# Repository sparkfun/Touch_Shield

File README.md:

**NOTE:** *This product has been retired from our catalog. If you are looking for more up-to-date info, please check out some of these resources to see how other users are still hacking and improving on this product.*
* *[SparkFun Forum](https://forum.sparkfun.com/)*
* *[Comments Here on GitHub](https://github.com/sparkfun/Touch_Shield/issues)*
* *[IRC Channel](https://www.sparkfun.com/news/263)*

Touch Shield
============

[  
*Touch Shield (DEV-12013)*](https://www.sparkfun.com/products/12013)

The Touch Shield allows you to easily interface the MPR121 IC to your Arduino. It has 9 capacitive touch pads,
with headers for the remaining 3 electrode connections. 

Repository Contents
-------------------
* **/Firmware** - Example firmware for interfacing with the Touch Shield
* **/Hardware** - All Eagle board design files (.brd, .sch)
* **/Production** - Test bed files and production panel files

Product Versions
----------------
* [DEV-10508](https://www.sparkfun.com/products/10508)- Basic Touch Shield
* [RTL-10774](https://www.sparkfun.com/products/10774)- Retail packaging of the Touch Shield and Arduino stackable headers

Version History
---------------
* [DEV-10508](https://www.sparkfun.com/products/10508) Version 1.1

License Information
-------------------
The hardware is released under [Creative Commons Share-alike 3.0](http://creativecommons.org/licenses/by-sa/3.0/).  
All other code is open source so please feel free to do anything you want with it; you buy me a beer if you use this and we meet someday ([Beerware license](http://en.wikipedia.org/wiki/Beerware)).

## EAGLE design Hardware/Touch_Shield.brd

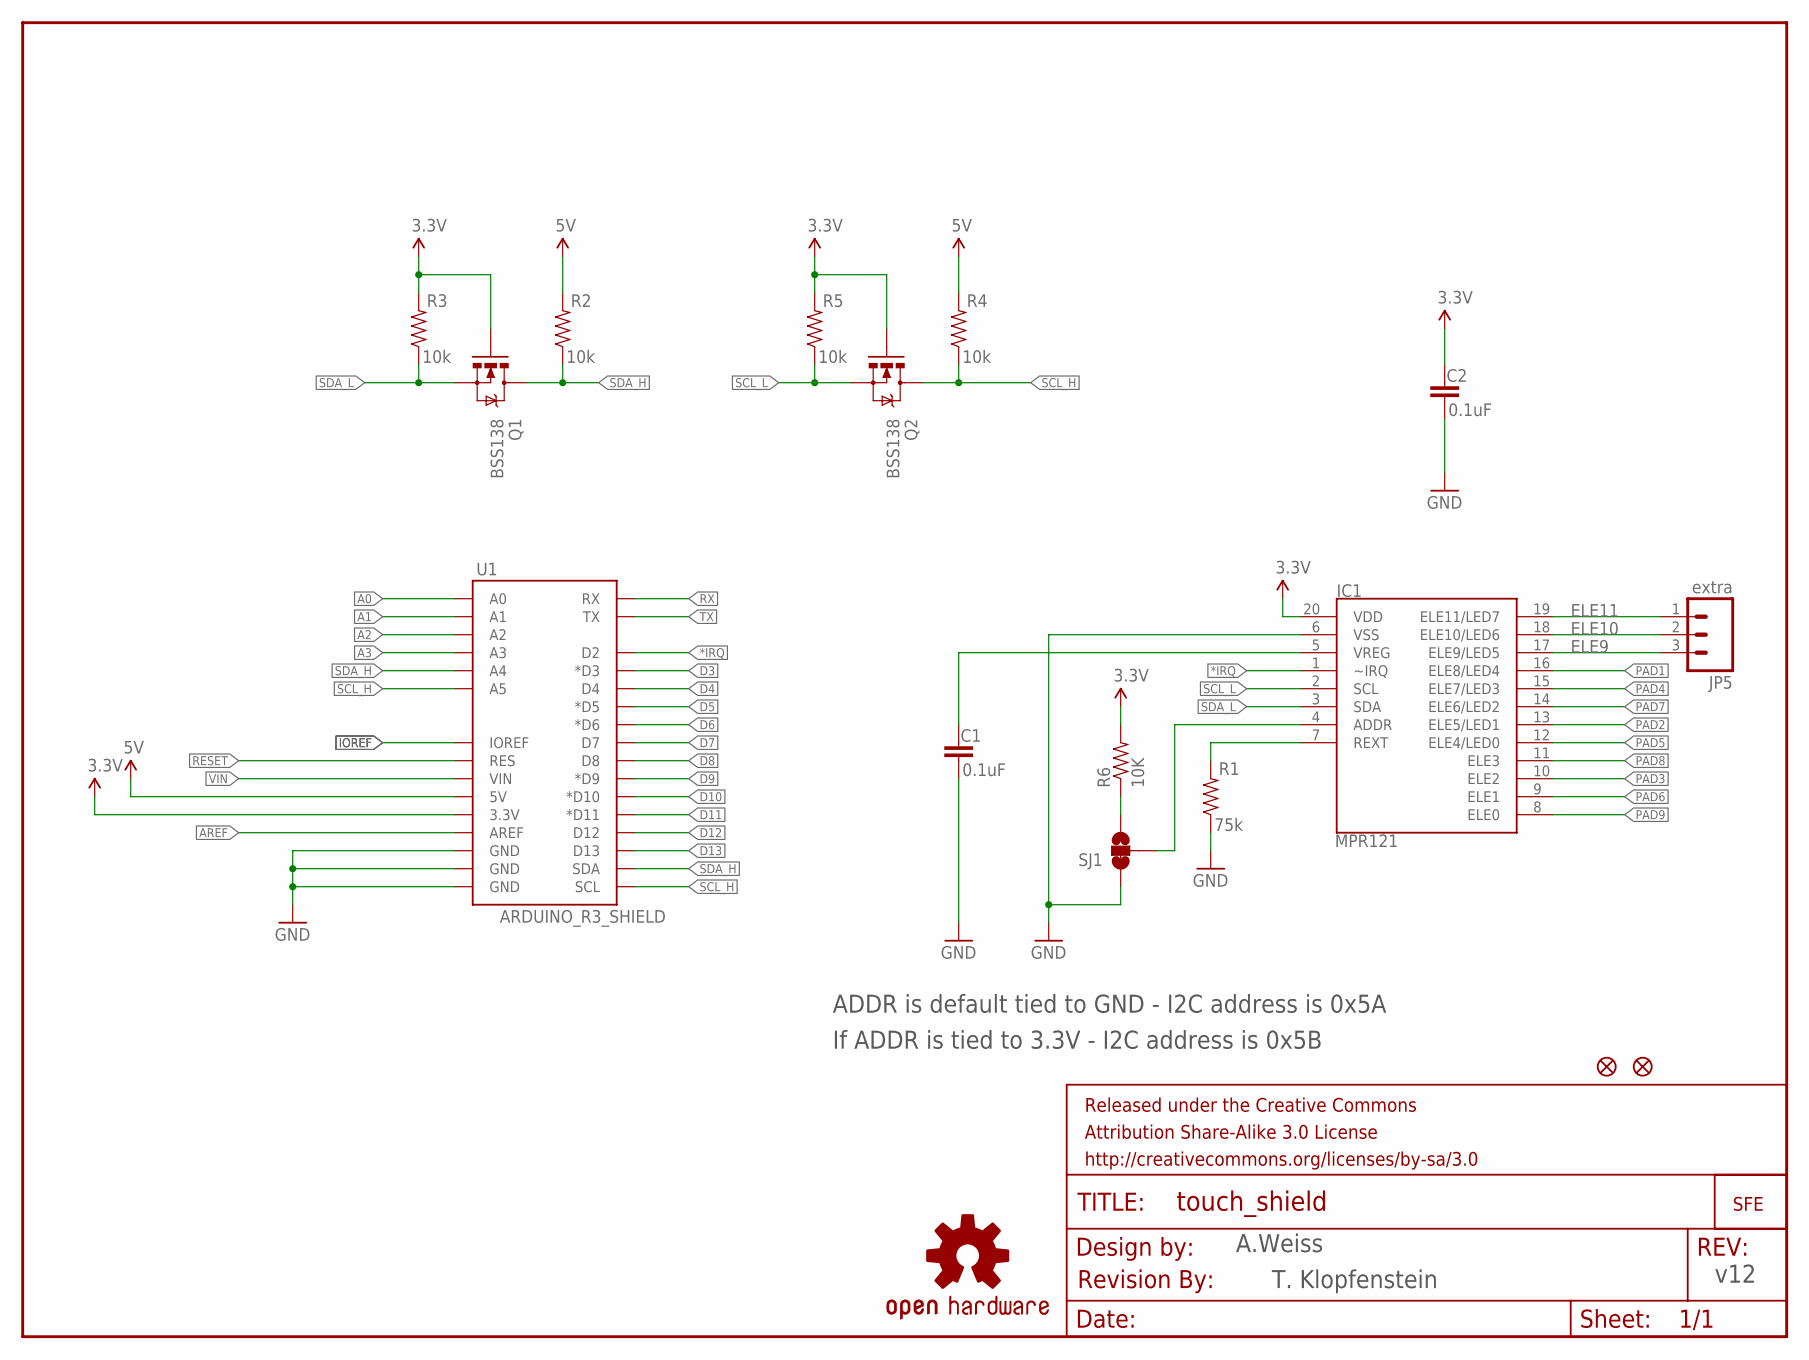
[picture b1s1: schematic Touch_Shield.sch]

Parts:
C1, C2: 0.1uF; 0603-CAP
FID1, FID2: FIDUCIALUFIDUCIAL; MICRO-FIDUCIAL
FRAME1: FRAME-LETTER; CREATIVE_COMMONS
IC1: MPR121; QFN-20-0.4MM-V2
JP1: LOGO-SFENEW; SFE-NEW-WEBLOGO
JP5: extra; 1X03
Q1, Q2: BSS138; SOT23-3
R1: 75k; 0603-RES
R2, R3, R4, R5: 10k; 0603-RES
R6: 10K; 0603-RES
SJ1: SOLDERJUMPER_2WAYPASTE1&2; SJ_3_PASTE1&2
U1: ARDUINO_R3_SHIELD; UNO_R3_SHIELD
U$1: REVISION
U$5: OSHW-LOGOL; OSHW-LOGO-L

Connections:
3.3V: C2.1, IC1.20 (VDD), Q1.1 (G), Q2.1 (G), R3.2, R5.2, R6.2, U1.3.3V
5V: R2.2, R4.2, U1.5V
*IRQ: IC1.1 (~IRQ), U1.D2
A0: U1.A0
A1: U1.A1
A2: U1.A2
A3: U1.A3
AREF: U1.AREF
D3: U1.D3 (*D3)
D4: U1.D4
D5: U1.D5 (*D5)
D6: U1.D6 (*D6)
D7: U1.D7
D8: U1.D8
D9: U1.D9 (*D9)
D10: U1.D10 (*D10)
D11: U1.D11 (*D11)
D12: U1.D12
D13: U1.D13
ELE9: IC1.17 (ELE9/LED5), JP5.3
ELE10: IC1.18 (ELE10/LED6), JP5.2
ELE11: IC1.19 (ELE11/LED7), JP5.1
GND: C1.2, C2.2, IC1.6 (VSS), R1.1, SJ1.1, U1.GND@0 (GND), U1.GND@1 (GND), U1.GND@2 (GND)
IOREF: U1.IOREF
unnamed: IC1.4 (ADDR), SJ1.2
unnamed: R6.1, SJ1.3
PAD1: IC1.16 (ELE8/LED4)
PAD2: IC1.13 (ELE5/LED1)
PAD3: IC1.10 (ELE2)
PAD4: IC1.15 (ELE7/LED3)
PAD5: IC1.12 (ELE4/LED0)
PAD6: IC1.9 (ELE1)
PAD7: IC1.14 (ELE6/LED2)
PAD8: IC1.11 (ELE3)
PAD9: IC1.8 (ELE0)
RESET: U1.RES
REXT: IC1.7 (REXT), R1.2
RX: U1.RX
SCL_H: Q2.3 (D), R4.1, U1.A5, U1.SCL
SCL_L: IC1.2 (SCL), Q2.2 (S), R5.1
SDA_H: Q1.3 (D), R2.1, U1.A4, U1.SDA
SDA_L: IC1.3 (SDA), Q1.2 (S), R3.1
TX: U1.TX
VIN: U1.VIN
VREG: C1.1, IC1.5 (VREG)

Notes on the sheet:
A.Weiss
ADDR is default tied to GND - I2C address is 0x5A
v12
T. Klopfenstein
If ADDR is tied to 3.3V - I2C address is 0x5B

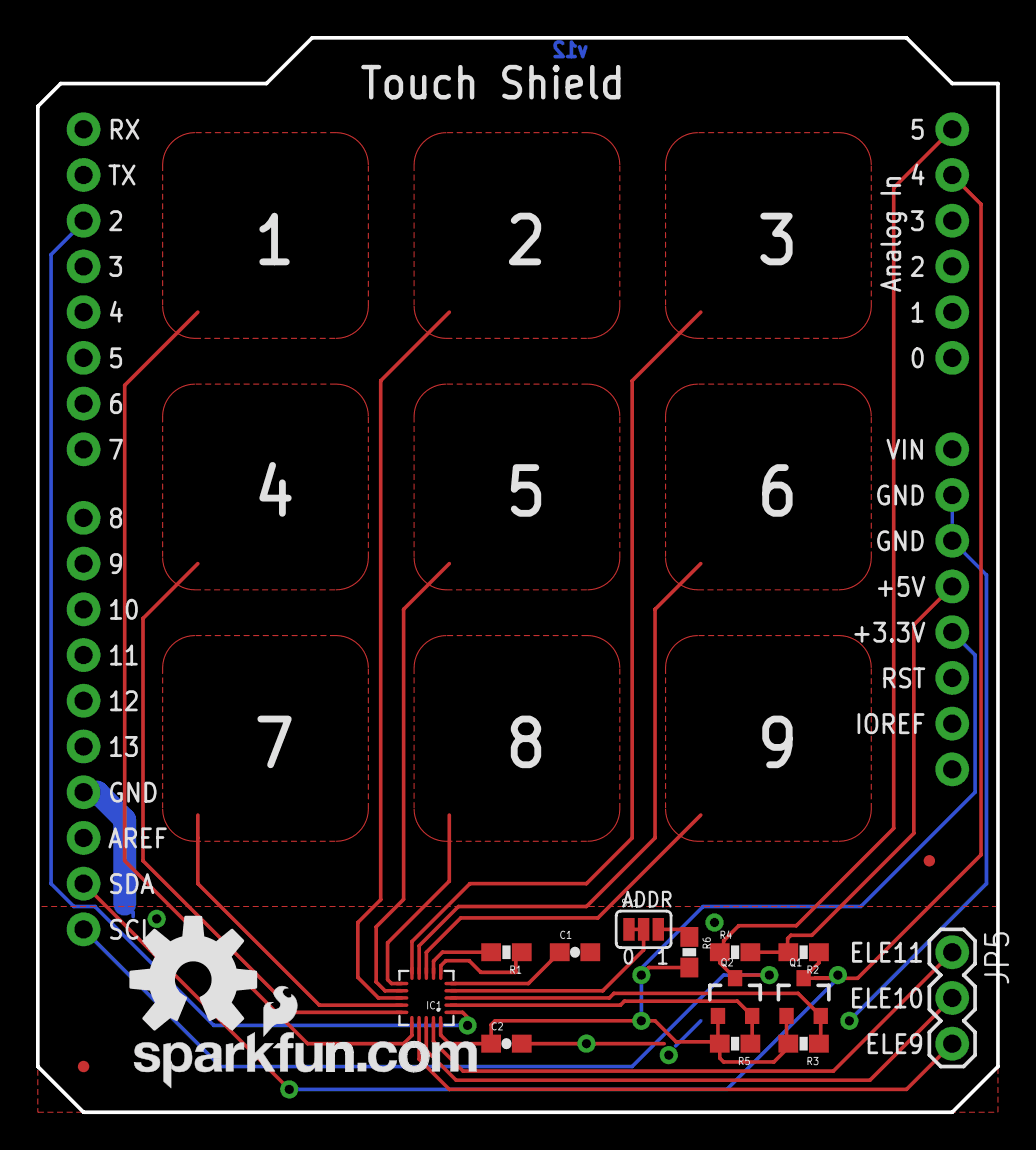
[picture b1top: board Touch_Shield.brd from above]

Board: 2 copper layers, 53.3 x 59.7 mm, 20 parts (0 on the bottom side), 15 nets.

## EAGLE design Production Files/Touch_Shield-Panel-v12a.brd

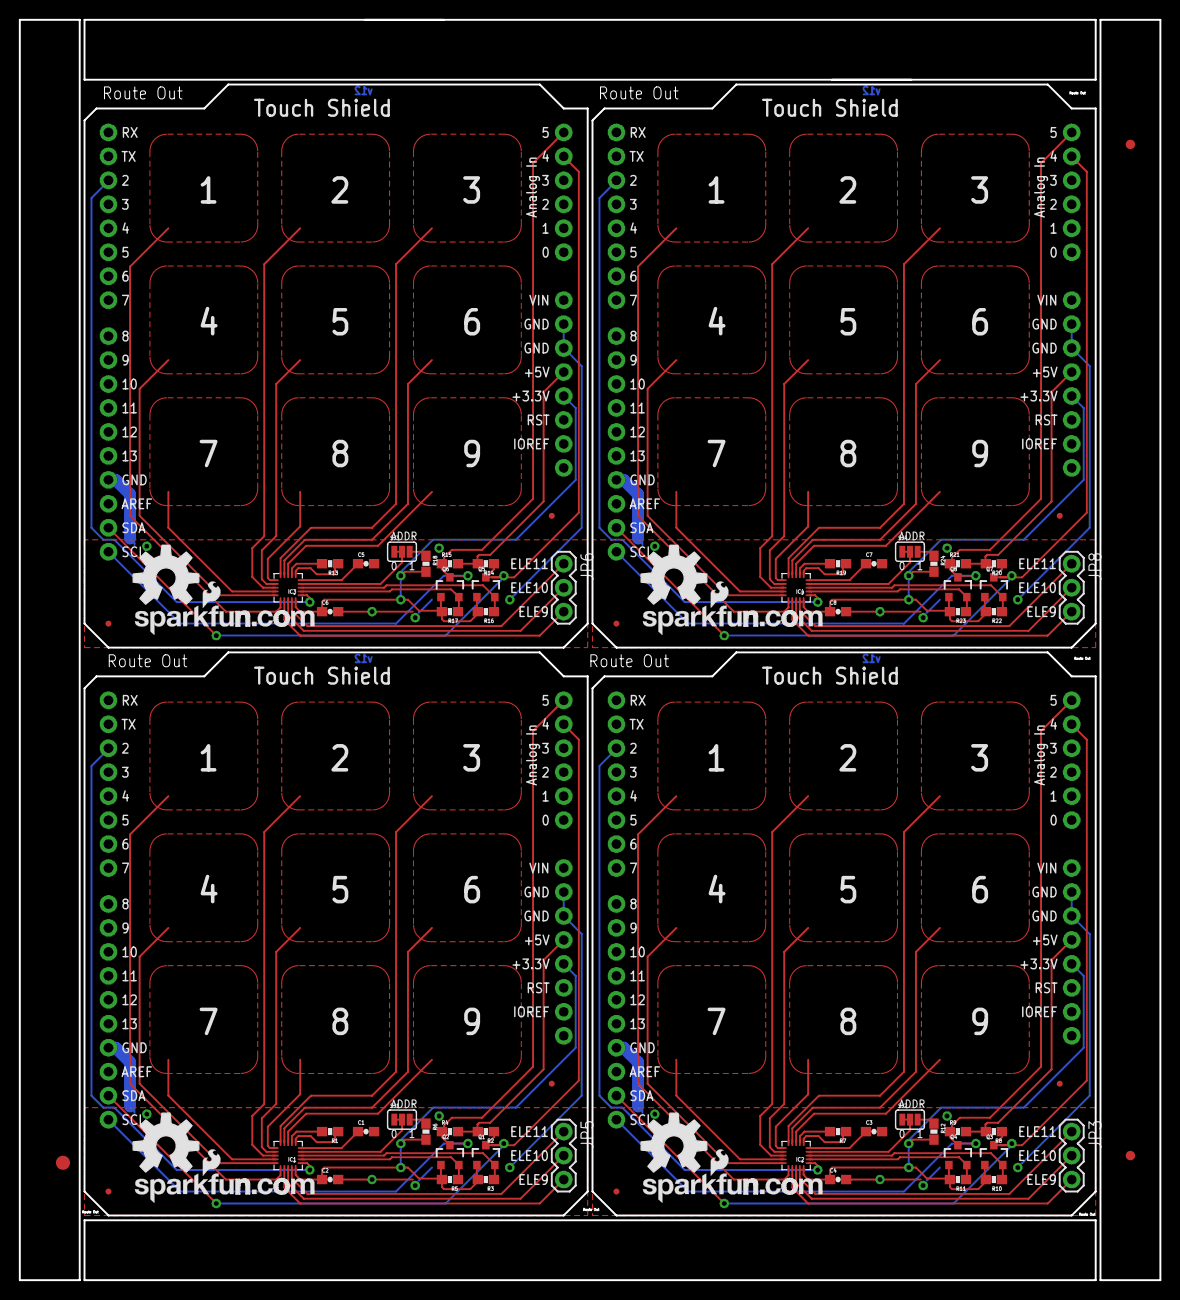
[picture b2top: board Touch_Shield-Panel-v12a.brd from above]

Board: 2 copper layers, 120.9 x 133.6 mm, 75 parts (0 on the bottom side), 60 nets.

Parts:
C1, C2, C3, C4, C5, C6, C7, C8: 0.1uF; 0603-CAP
E$1: FIDUCIAL-1.5X3
E$4, E$8: FIDUCIAL-1X2
FID1, FID2, FID3, FID4, FID5, FID6, FID7, FID8: FIDUCIALUFIDUCIAL; MICRO-FIDUCIAL
IC1, IC2, IC3, IC4: MPR121; QFN-20-0.4MM-V2
JP1, JP2, JP4, JP7: LOGO-SFENEW; SFE-NEW-WEBLOGO
JP3, JP5, JP6, JP8: extra; 1X03
Q1, Q2, Q3, Q4, Q5, Q6, Q7, Q8: BSS138; SOT23-3
R1, R7, R13, R19: 75k; 0603-RES
R2, R3, R4, R5, R8, R9, R10, R11, R14, R15, R16, R17, R20, R21, R22, R23: 10k; 0603-RES
R6, R12, R18, R24: 10K; 0603-RES
SJ1, SJ2, SJ3, SJ4: SJ_3_PASTE1&2
U1, U2, U3, U4: ARDUINO_R3_SHIELD; UNO_R3_SHIELD
U$1, U$2, U$3, U$5: OSHW-LOGOL; OSHW-LOGO-L

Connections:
3.3V: C2.1, IC1.20, Q1.1, Q2.1, R3.2, R5.2, R6.2, U1.3.3V
3.3V1: C4.1, IC2.20, Q3.1, Q4.1, R10.2, R11.2, R12.2, U2.3.3V
3.3V2: C6.1, IC3.20, Q5.1, Q6.1, R16.2, R17.2, R18.2, U3.3.3V
3.3V3: C8.1, IC4.20, Q7.1, Q8.1, R22.2, R23.2, R24.2, U4.3.3V
5V: R2.2, R4.2, U1.5V
5V1: R8.2, R9.2, U2.5V
5V2: R14.2, R15.2, U3.5V
5V3: R20.2, R21.2, U4.5V
*IRQ: IC1.1, U1.D2
*IRQ1: IC2.1, U2.D2
*IRQ2: IC3.1, U3.D2
*IRQ3: IC4.1, U4.D2
ELE1: IC2.19, JP3.1
ELE2: IC2.18, JP3.2
ELE3: IC2.17, JP3.3
ELE4: IC3.19, JP6.1
ELE5: IC3.18, JP6.2
ELE6: IC3.17, JP6.3
ELE7: IC4.19, JP8.1
ELE8: IC4.18, JP8.2
ELE9: IC1.17, JP5.3
ELE10: IC1.18, JP5.2
ELE11: IC1.19, JP5.1
ELE12: IC4.17, JP8.3
GND: C1.2, C2.2, IC1.6, R1.1, SJ1.1, U1.GND@0, U1.GND@1, U1.GND@2
GND1: C3.2, C4.2, IC2.6, R7.1, SJ2.1, U2.GND@0, U2.GND@1, U2.GND@2
GND2: C5.2, C6.2, IC3.6, R13.1, SJ3.1, U3.GND@0, U3.GND@1, U3.GND@2
GND3: C7.2, C8.2, IC4.6, R19.1, SJ4.1, U4.GND@0, U4.GND@1, U4.GND@2
unnamed: IC1.4, SJ1.2
unnamed: R6.1, SJ1.3
unnamed: IC2.4, SJ2.2
unnamed: R12.1, SJ2.3
unnamed: IC3.4, SJ3.2
unnamed: R18.1, SJ3.3
unnamed: IC4.4, SJ4.2
unnamed: R24.1, SJ4.3
REXT: IC1.7, R1.2
REXT1: IC2.7, R7.2
REXT2: IC3.7, R13.2
REXT3: IC4.7, R19.2
SCL_H: Q2.3, R4.1, U1.A5, U1.SCL
SCL_H1: Q4.3, R9.1, U2.A5, U2.SCL
SCL_H2: Q6.3, R15.1, U3.A5, U3.SCL
SCL_H3: Q8.3, R21.1, U4.A5, U4.SCL
SCL_L: IC1.2, Q2.2, R5.1
SCL_L1: IC2.2, Q4.2, R11.1
SCL_L2: IC3.2, Q6.2, R17.1
SCL_L3: IC4.2, Q8.2, R23.1
SDA_H: Q1.3, R2.1, U1.A4, U1.SDA
SDA_H1: Q3.3, R8.1, U2.A4, U2.SDA
SDA_H2: Q5.3, R14.1, U3.A4, U3.SDA
SDA_H3: Q7.3, R20.1, U4.A4, U4.SDA
SDA_L: IC1.3, Q1.2, R3.1
SDA_L1: IC2.3, Q3.2, R10.1
SDA_L2: IC3.3, Q5.2, R16.1
SDA_L3: IC4.3, Q7.2, R22.1
VREG: C1.1, IC1.5
VREG1: C3.1, IC2.5
VREG2: C5.1, IC3.5
VREG3: C7.1, IC4.5

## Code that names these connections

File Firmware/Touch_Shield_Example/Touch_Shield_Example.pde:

/* 
 Touch Shield Example using the MPR121 touch sensor IC 

 by: Aaron Weiss, based on the MPR121 Keypad Example by Jim Lindblom
     
 SparkFun Electronics
 created on: 5/12/11
 license: OSHW 1.0, http://freedomdefined.org/OSHW
 
 Pressing a pad will print the corresponding number.
 
 Hardware: 3.3V or 5V Arduino

 Notes: The Wiring library is not used for I2C, a default atmel I2C lib
        is used. Be sure to keep the .h files with the project. 
*/

// include the atmel I2C libs
#include "mpr121.h"
#include "i2c.h"

// 11 max digits used
#define DIGITS 11 

// Match key inputs with electrode numbers
#define ONE 8
#define TWO 5
#define THREE 2
#define FOUR 7
#define FIVE 4
#define SIX 1
#define SEVEN 6
#define EIGHT 3
#define NINE 0

//extras (not used)
#define ELE9 9
#define ELE10 10
#define ELE11 11

//interupt pin
int irqpin = 2;  // D2

void setup()
{
  //make sure the interrupt pin is an input and pulled high
  pinMode(irqpin, INPUT);
  digitalWrite(irqpin, HIGH);
  
  //configure serial out
  Serial.begin(9600);
  
  //output on ADC4 (PC4, SDA)
  DDRC |= 0b00010011;
  // Pull-ups on I2C Bus
  PORTC = 0b00110000; 
  // initalize I2C bus. Wiring lib not used. 
  i2cInit();
  
  delay(100);
  // initialize mpr121
  mpr121QuickConfig();
  
  // Create and interrupt to trigger when a button
  // is hit, the IRQ pin goes low, and the function getNumber is run. 
  attachInterrupt(0,getNumber,LOW);
  
  // prints 'Ready...' when you can start hitting numbers
  Serial.println("Ready...");
}

void loop()
{
  //You can put additional code here. The interrupt will run in the backgound. 
}

void getNumber()
{
  int i = 0;
  int touchNumber = 0;
  uint16_t touchstatus;
  char digits[DIGITS];
  
  touchstatus = mpr121Read(0x01) << 8;
  touchstatus |= mpr121Read(0x00);
  
  for (int j=0; j<12; j++)  // Check how many electrodes were pressed
  {
    if ((touchstatus & (1<<j)))
      touchNumber++;
  }
  
  if (touchNumber == 1)
  {
    if (touchstatus & (1<<SEVEN))
      digits[i] = '7';
    else if (touchstatus & (1<<FOUR))
      digits[i] = '4';
    else if (touchstatus & (1<<ONE))
      digits[i] = '1';
    else if (touchstatus & (1<<EIGHT))
      digits[i] = '8';
    else if (touchstatus & (1<<FIVE))
      digits[i] = '5';
    else if (touchstatus & (1<<TWO))
      digits[i] = '2';
    else if (touchstatus & (1<<NINE))
      digits[i] = '9';
    else if (touchstatus & (1<<SIX))
      digits[i] = '6';
    else if (touchstatus & (1<<THREE))
      digits[i] = '3';
      
    Serial.print(digits[i]);
    i++;
  }
  //do nothing if more than one button is pressed
  else if (touchNumber == 0)
    ;
  else
    ;
}

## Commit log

2013-07-30 Update board files, adding README and Firmware to repo
2013-07-30 Adding schematic note about selectable I2C address
2013-08-07 Updating shield layout to R3
2013-08-07 Updating all the resistors to the same production ID number
2013-10-01 Created Panel
2013-12-17 Updating README with new version information
2013-12-18 Re-panelized and added fiducials to board
    I re-did the panel to 4 boards and added local fiducials

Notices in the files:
parts and their libraries:
SparkFun-Aesthetics: Licensing: CC v3.0 Share-Alike You are welcome to use this library for commercial purposes.
SparkFun-Aesthetics: Released under the Creative Commons Attribution Share-Alike 3.0 License
SparkFun-Aesthetics: Released under the Creative Commons
